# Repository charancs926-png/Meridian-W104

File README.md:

# Meridian W104

Meridian W104 is my custom full size **104-key wireless mechanical keyboard**, built around a **Seeed XIAO nRF52840 non-Plus**.

so basically i wanted a full size board with a proper number pad that could run over bluetooth, but still use usb-c when needed. the project brings together the key matrix, diodes, serial scan logic, battery connection and a slim rounded case. the hardware is in KiCad and the case source is in Fusion 360, with the files needed to make a first prototype included here.

## why i made this

i wanted to understand how a complete keyboard fits together, from what happens when a switch closes to how that key reaches the computer. keeping the numpad and navigation block was important, and i wanted the enclosure to feel like one finished design instead of a box around a PCB.

main goals for this project :

- make a full size ANSI board with 104 keys, navigation keys and numpad
- use **Bluetooth LE** with a protected single-cell battery, plus usb-c
- scan the large matrix using one 74HC595 and three 74HC165 registers
- keep the schematic on one sheet and the board routing orderly
- build a slim rounded case with a bronze seam accent and concealed screws
- learn the complete sequence: schematic → PCB layout → CAD → fabrication → firmware bring-up

the tricky parts were making the matrix and firmware agree, keeping the radio antenna clear, and checking that the screws and battery actually fit the case. those checks matter just as much as the overall appearance.

## project status

this is the final digital **V1 first-prototype fabrication package**. the latest review on 9 October 2026 passed the configured KiCad electrical and board checks with zero errors and zero unconnected items. firmware simulation covers all 104 populated keys. the five printable meshes are closed, and the retained full STEP check covers 219 valid solids. physical soldering, typing, BLE range, charging and print-fit testing are the next stage.

whats included :

- editable KiCad project, one-page schematic, PCB, local libraries and 104 linked switch models
- complete assembly `.step`
- five printable `.stl` parts, with printing and assembly instructions
- Gerber/drill ZIP, assembly BOM, placement files and release checks
- CircuitPython USB/BLE firmware and a matrix diagnostic
- schematic/PCB PDFs, project images, cart evidence

current hardware summary :

| | |
|---|---|
| Layout | full size ANSI, 104 keys including nav block and numpad |
| Controller | Seeed XIAO nRF52840, original non-Plus |
| Connectivity | Bluetooth LE and usb-c; rear mode button switches transport |
| Matrix | 6 rows × 22 columns, 104 populated positions |
| Scan logic | 1× 74HC595 row register, 3× 74HC165 column registers, 3.3V |
| Diodes | 104× 1N4148W, one per switch |
| Battery | protected 3.7V 500mAh 502248P, with a separate PH2.0 pigtail |
| Indicators | Caps Lock, Num Lock and Scroll Lock; Num LED blinks while waiting for BLE |
| Stabilizers | Durock V2 PCB screw-in set: seven 2U plus one 6.25U |
| Switches | soldered MX-compatible PCB pattern; listed Haku pack selection |
| Keycaps | ANSI MX set with 6.25U spacebar; white Cherry-profile selection |
| Case | rounded printed bottom, frame, plate, bronze accent and mode-button cap |
| PCB | four copper layers, 1.6mm FR4; nominal 458.15 × 164mm |

the Meridian look comes from the rounded frame, recessed rear controls and thin accent seam. the white keycaps keep the full size layout easy to read. these are design renders; a finished physical keyboard has not been photographed yet.

## images

### full 3d model

### indicator leds (caps / num / scroll)

the three lock indicators sit in the rear strip. the PCB view also shows the switches and controller placement.

### pcb

### schematic / wiring

the complete matrix, XIAO, four scan registers, battery wiring, switches and lock indicators are on one A2 sheet. the [PDF](PDFs/Meridian%20W104.pdf) can be zoomed to read individual values and pins.

### other screenshots

some more views of the case and plate from Fusion :

## repo file checklist

important files in this repo :

- `PCB/Meridian W104.kicad_pro`
- `PCB/Meridian W104.kicad_sch`
- `PCB/Meridian W104.kicad_pcb`
- `PCB/3D Models/` — portable switch models and attribution
- `CAD/Full Meridian W104/Meridian W104.step`
- `CAD/Printing Files/` — `Bottom.stl`, `Plate.stl`, `Top Frame.stl`, `Bronze Seam Accent.stl`, `Mode Button.stl`
- `Firmware/boot.py`, `code.py`, `scanner.py`, `keymap.py`, `matrix_diagnostic.py`
- `Fabrication/Assembly BOM.csv`
- `Fabrication/Component Positions.csv` and `SMD Positions.csv`
- `Fabrication/netlist.ipc` — IPC-D-356 bare-board test netlist
- `Fabrication/Meridian-W104-PCB-Fabrication.zip`
- `Fabrication/Gerbers/` — individual plots, job and drill files
- `bom.csv`
- `PDFs/Meridian W104.pdf` — chematic page
- `PDFs/PCB Editor.pdf` — PCB layer pages
- `JOURNAL.md`

## cad

the case source is in **Fusion 360**, with a full `.step` export in `CAD/Full Meridian W104/`. only the five parts that need printing are in `CAD/Printing Files/`. all dimensions are millimetres; the largest part spans **466.15mm**, so the printer needs enough real usable bed area, including space for a brim.

## firmware note

the firmware is **CircuitPython** with a custom serial-matrix scanner. the normal files are `boot.py`, `code.py`, `scanner.py` and `keymap.py`; `matrix_diagnostic.py` is the separate bring-up tool.

install the official [XIAO nRF52840 CircuitPython build](https://circuitpython.org/board/Seeed_XIAO_nRF52840_Sense/) after checking that page's bootloader prerequisite, then copy the four normal files and `adafruit_ble`, `adafruit_hid` plus their dependencies from the matching [library bundle](https://circuitpython.org/libraries) to `CIRCUITPY`. the family download also covers the original non-Sense module used here.

usb insertion/removal selects the available transport. a short press and release of the rear mode button toggles USB/BLE; holding it for five seconds clears BLE bonding. the advertised name is **Meridian W104**. reports support six ordinary keys plus modifiers. test the diagnostic with all 104 real switches before closing the case; simulation is already passing, but soldered hardware still needs bring-up.

## bom (summary)

full BOM is in `bom.csv`. these are recorded carts, supplier listings and a PCB quote, **not a record of paid orders**. prices below are totals for each row, including the stated retailer packs; the CSV notes explain fitted quantities and spares.

| # | Name | Purpose | Qty | Cost (INR) | Cost ($) | Distributor | Link |
|---|---|---|---:|---:|---:|---|---|
| 1 | XIAO nRF52840 non-Plus | BLE / USB controller and module charger | 1 | 1,451.00 | 15.06 | LionCircuits | [View](https://www.lioncircuits.com/parts/102010448) |
| 2 | SN74HC595D SOIC-16 | 6 row sink outputs | 1 | 32.20 | 0.33 | KTRON | [View](https://www.ktron.in/product/74hc595d-8-bit-shift-register-ic-smd/) |
| 3 | SN74HC165D SOIC-16 | 22 column samples | 3 | 59.40 | 0.62 | KTRON | [View](https://www.ktron.in/product/74hc165d-ic-8-bit-shift-register-soic-16-nxp/) |
| 4 | Cherry MX PCB-pattern switch, 5-pin | Soldered keys | 104 | 3,850.00 | 39.96 | StacksKB | [View](https://stackskb.com/store/menel-eight-nine-haku-linear-switch-pack-of-10/) |
| 5 | 1N4148W SOD-123 | Per-key isolation | 104 | 108.16 | 1.12 | Robu | [View](https://robu.in/product/1n4148w-slkor-75v-1v-4ns-150ma-sod-123-switching-diodes-rohs/) |
| 6 | 22k 0805 1% resistor | Column bias | 22 | 10.08 | 0.10 | Robu | [View](https://robu.in/product/ac0805fr-0722kl-yageo-res-thick-film-0805-22k-ohm-1-0-125w1-8w-%c2%b1100ppm-c-pad-smd-t-r-automotive-aec-q200/) |
| 7 | 1k 0805 resistor | Lock indicator current limit | 3 | 13.80 | 0.14 | Robu | [View](https://robu.in/product/rc0805jr-071kl-yageo-res-thick-film-0805-1k-ohm-5-0-125w1-8w-%c2%b1100ppm-c-pad-smd-t-r/) |
| 8 | 100k 0805 resistor | Row output enable default OFF | 1 | 13.50 | 0.14 | Robu | [View](https://robu.in/product/0805w8f1003t5e-uniohm-royal-ohm-125mw-thick-film-resistors-150v-%c2%b1100ppm-%e2%84%83%c2%b11-100k%cf%89-0805-chip-resistor-surface-mount-rohs/) |
| 9 | 100n 0805 X7R, 10V or above | Logic decoupling | 4 | 30.00 | 0.31 | Flyrobo | [View](https://www.flyrobo.in/0805-100nf-50v-chip-capacitors) |
| 10 | 10u 0805 X5R, 10V or above | Rail bulk capacitor | 1 | 10.60 | 0.11 | Robu | [View](https://robu.in/product/08053d106kat2a-kyocera-avx-smd-multilayer-ceramic-capacitor-10-%c2%b5f-25-v-0805-2012-metric-%c2%b1-10-x5r/) |
| 11 | 3mm LED, diffused, Vf compatible with 3.3V | Caps / Num / Scroll indicators | 3 | 18.80 | 0.20 | KTRON | [View](https://www.ktron.in/product/red-led-red-diffusion-3mm-th/) |
| 12 | JST PH S2B-PH-K horizontal 2-pin | Battery connector | 1 | 16.00 | 0.17 | Robu | [View](https://robu.in/product/s2b-ph-klfsn-jst-1x2p-2p-ph-tin-2-25%e2%84%8385%e2%84%83-2a-1-2mm-brass-bend-insert-push-pullp2mm-wire-to-board-connector-rohs/) |
| 13 | PCM12-pattern SMD SPDT slide switch | Battery disconnect | 1 | 66.00 | 0.68 | Robu | [View](https://robu.in/product/pcm12smtr-ck-standing-paste-single-pole-double-throw-spdt-6v-smd-slide-switches-rohs/) |
| 14 | 6mm THT tactile pushbutton | Transport toggle / bond reset | 1 | 3.00 | 0.03 | Tomson | [View](https://www.tomsonelectronics.com/products/tactile-push-button-micro-switch-6x6x4-3mm) |
| 15 | Protected 3.7V 500mAh LiPo 502248P (bare leads) | Wireless power; maximum assembled envelope 60x28x6mm | 1 | 299.00 | 3.10 | Probots | [View](https://probots.co.in/3-7v-500mah-lipo-battery-502248-open-ended.html) |
| 16 | JST-PH2.0 2-pin female pigtail to bare wire | Adapt protected bare-lead battery to J1 | 1 | 4.13 | 0.04 | Hubtronics | [View](https://hubtronics.in/connectors/relimate_connectors/board_to_wire_relimate/1508) |
| 17 | 7-pin 2.54mm headers | Module mounting; two rows | 2 | 40.00 | 0.42 | Flyrobo | [View](https://www.flyrobo.in/40-pin-male-header-connector-strip-breakable-5pcs) |
| 18 | Flexible insulated wire | Module underside BAT+ / BAT- leads | 2 | 24.00 | 0.25 | Robu | [View](https://robu.in/product/high-quality-ultra-flexible-28awg-silicone-wire-1000m-red/) |
| 19 | ANSI 104-key MX keycap set | User keycaps; 6.25u spacebar | 1 | 1,000.00 | 10.38 | StacksKB | [View](https://stackskb.com/store/stackspbt-blank-white-cherry-profile-keycaps-113-key/) |
| 20 | Durock V2 PCB screw-in stabilizer kit (7x2U + 1x6.25U) | Seven wide keys and 6.25U spacebar | 1 | 2,365.00 | 24.54 | StacksKB | [View](https://stackskb.com/store/durock-clear-screw-in-stabilizers-v2/?attribute_combination=7%2B1+Set&attribute_spacebar-size=6.25U) |
| 21 | M3x30mm DIN912 socket-head SS304 screws (10pc pack) | 3 concealed rear mounts | 1 | 116.00 | 1.20 | RPI Shop | [View](https://rpishop.in/products/ss-allen-cap-m3?variant=45146051510424) |
| 22 | M3x15mm DIN912 socket-head SS304 screws (10pc pack) | 3 concealed front mounts | 1 | 88.00 | 0.91 | RPI Shop | [View](https://rpishop.in/products/ss-allen-cap-m3?variant=45146051412120) |
| 23 | M3x20mm DIN912 socket-head SS304 screws (10pc pack) | 1 concealed centre mounts | 1 | 92.00 | 0.95 | RPI Shop | [View](https://rpishop.in/products/ss-allen-cap-m3?variant=45146051444888) |
| 24 | M3 insert assortment; select 5mm long x4.2mm OD | Seven top-frame bosses, 3.9mm pilot holes | 1 | 1,519.00 | 15.76 | Robu | [View](https://robu.in/product/brass-heat-set-insert-nut-hot-melt-knurled-threaded-m3-400pcs-kit/) |
| 25 | Meridian W104 four-layer PCB, 1.6mm | Final checked four-layer Gerber and drill package | 5 | 8,647.58 | 89.25 | JLCPCB | [View](https://cart.jlcpcb.com/shopcart/cart/) |
| 26 | Printed case set | Bottom, plate, top frame, seam accent, mode button | 1 | 0.00 | 0.00 | Printing Legion | [View](https://printlegion.hackclub.com/) |

**listed BOM total : ₹19,877.25 / $205.77**

---

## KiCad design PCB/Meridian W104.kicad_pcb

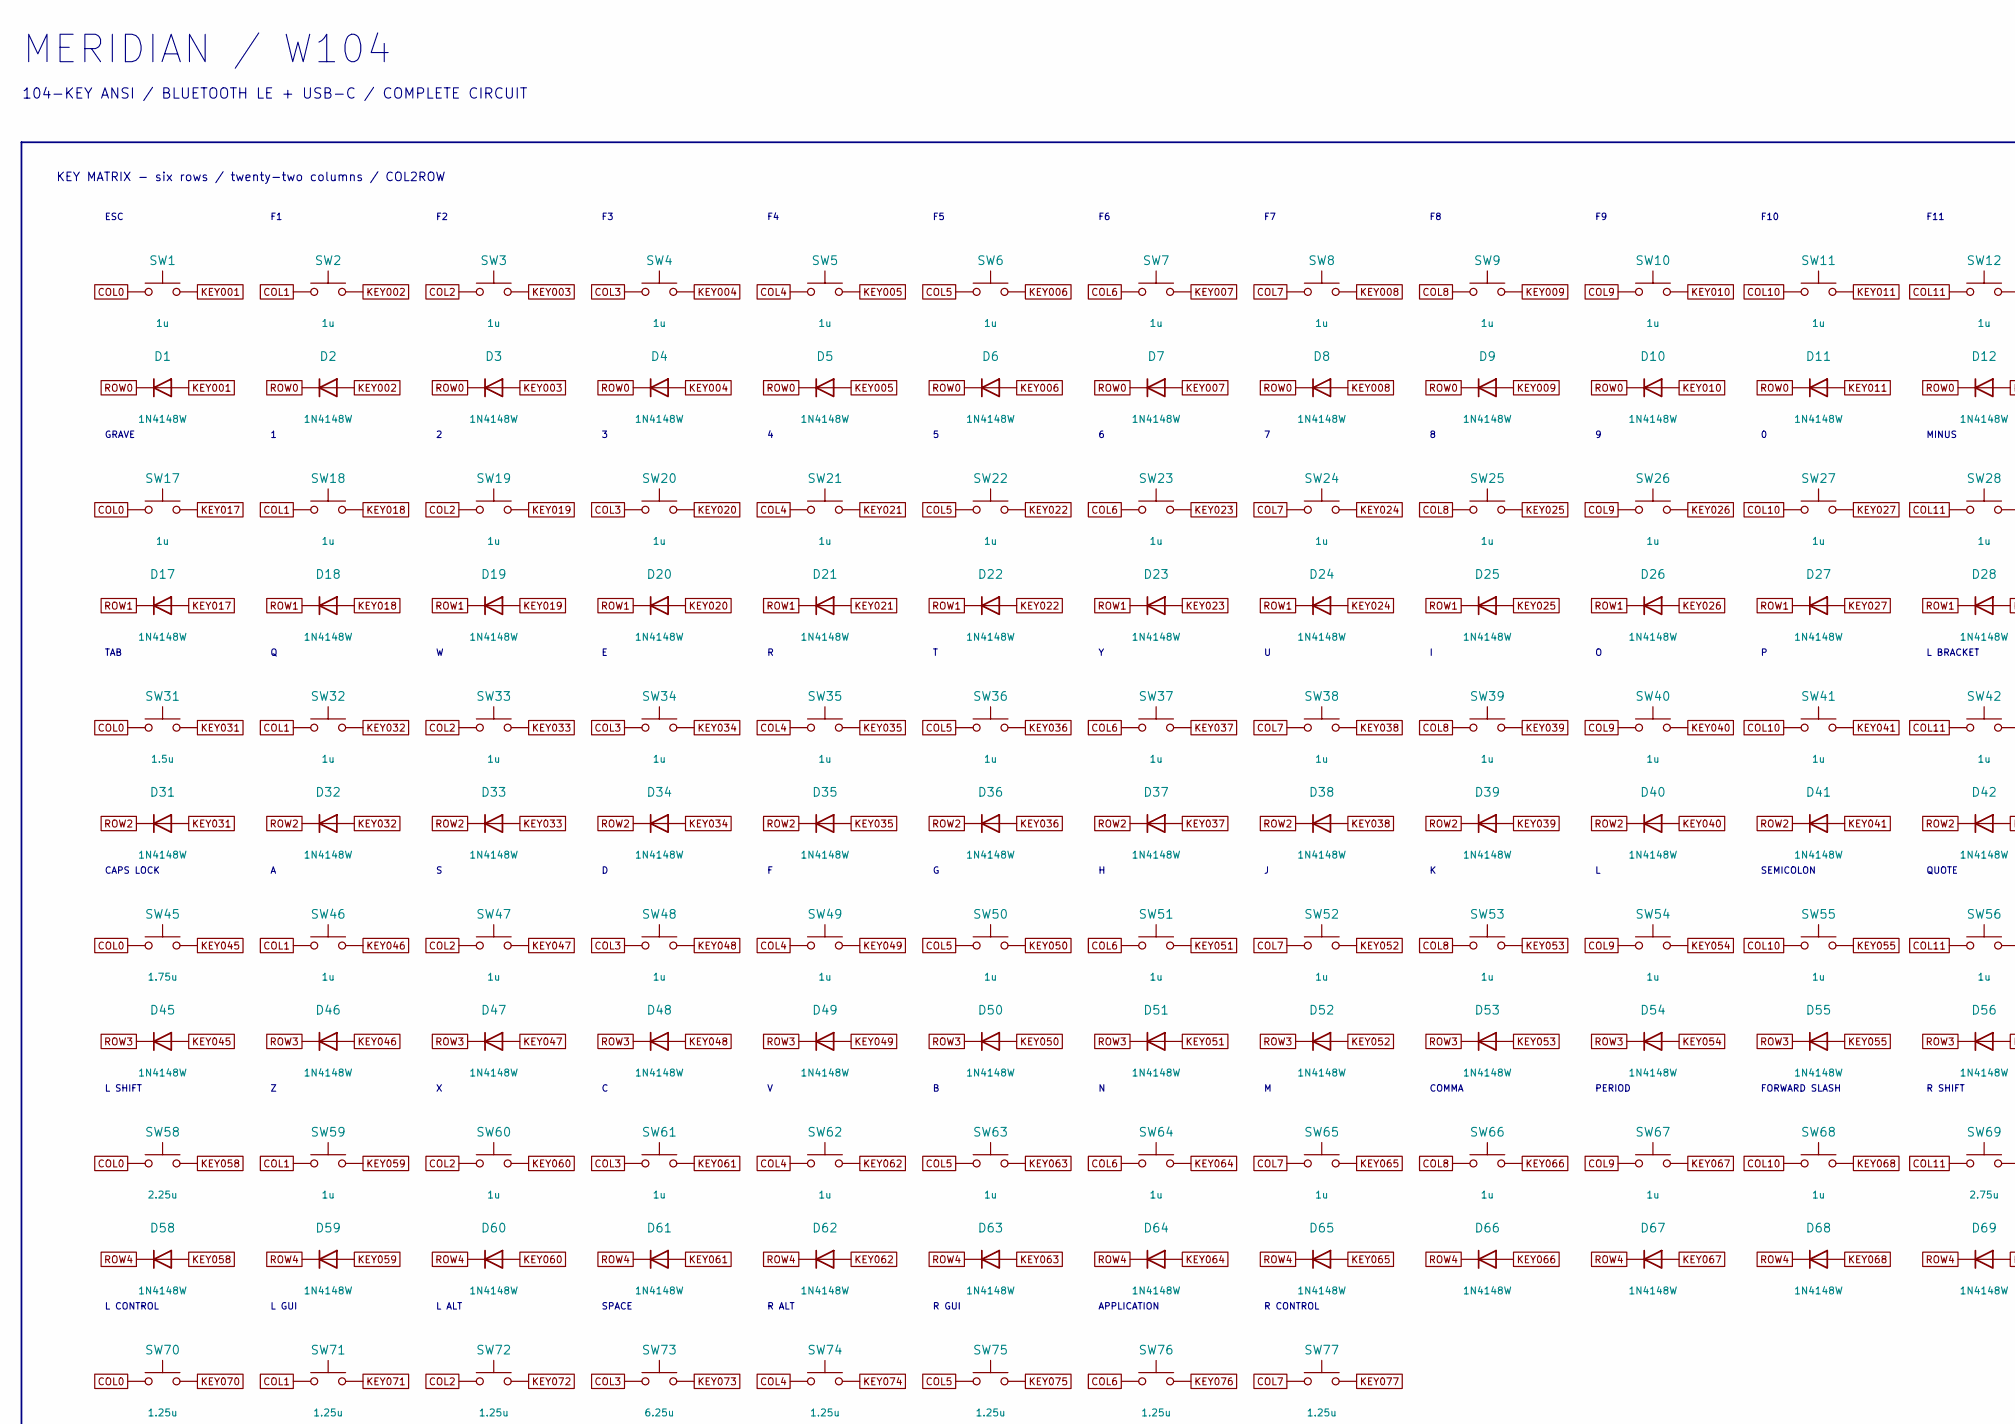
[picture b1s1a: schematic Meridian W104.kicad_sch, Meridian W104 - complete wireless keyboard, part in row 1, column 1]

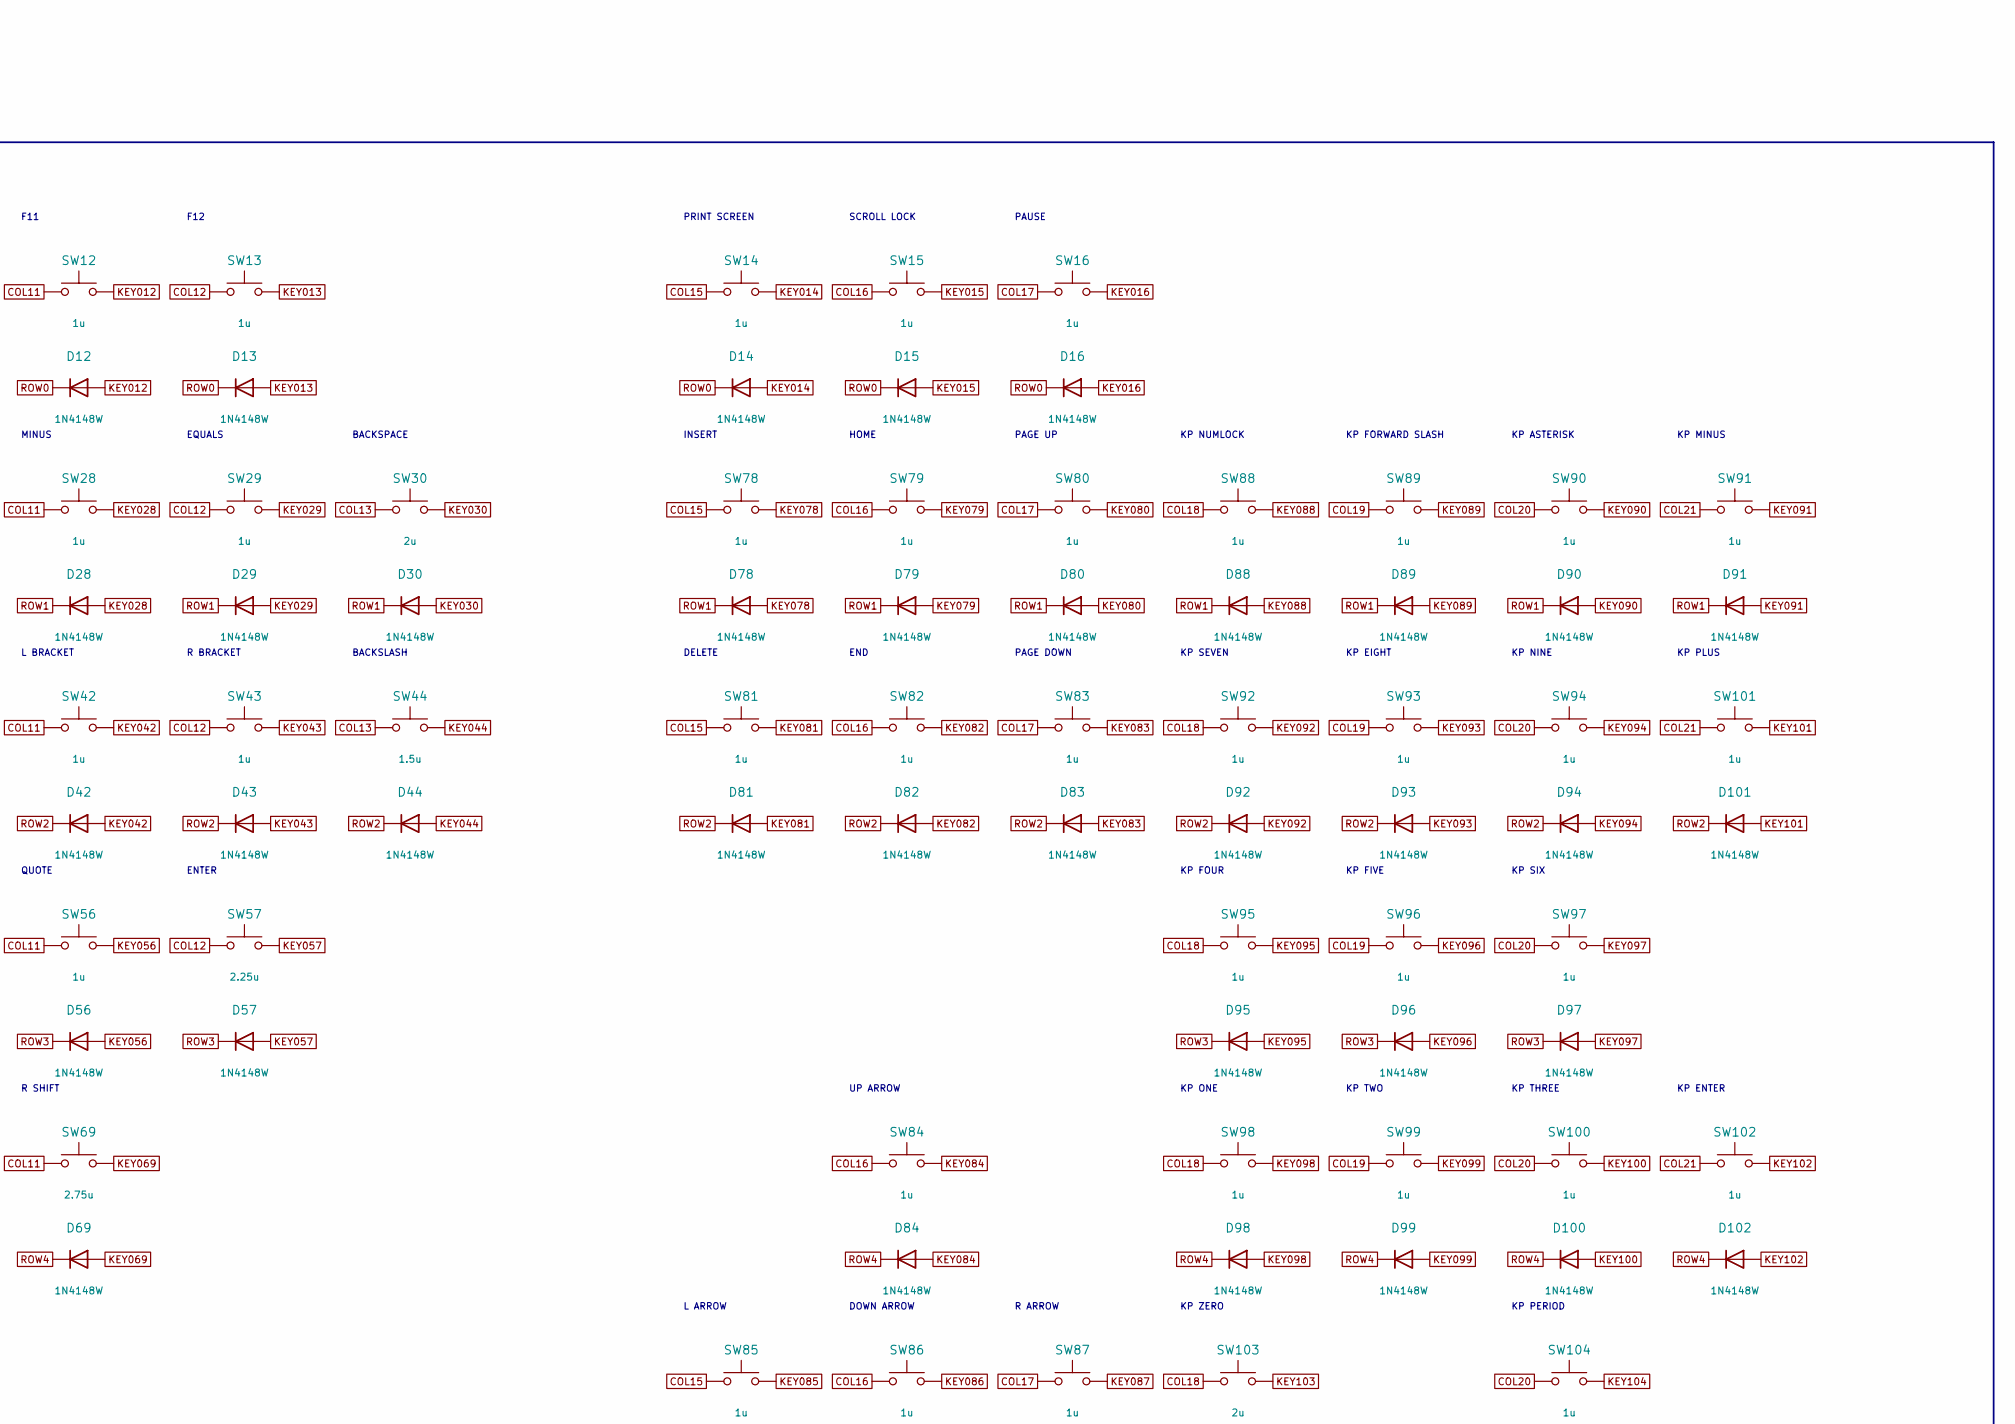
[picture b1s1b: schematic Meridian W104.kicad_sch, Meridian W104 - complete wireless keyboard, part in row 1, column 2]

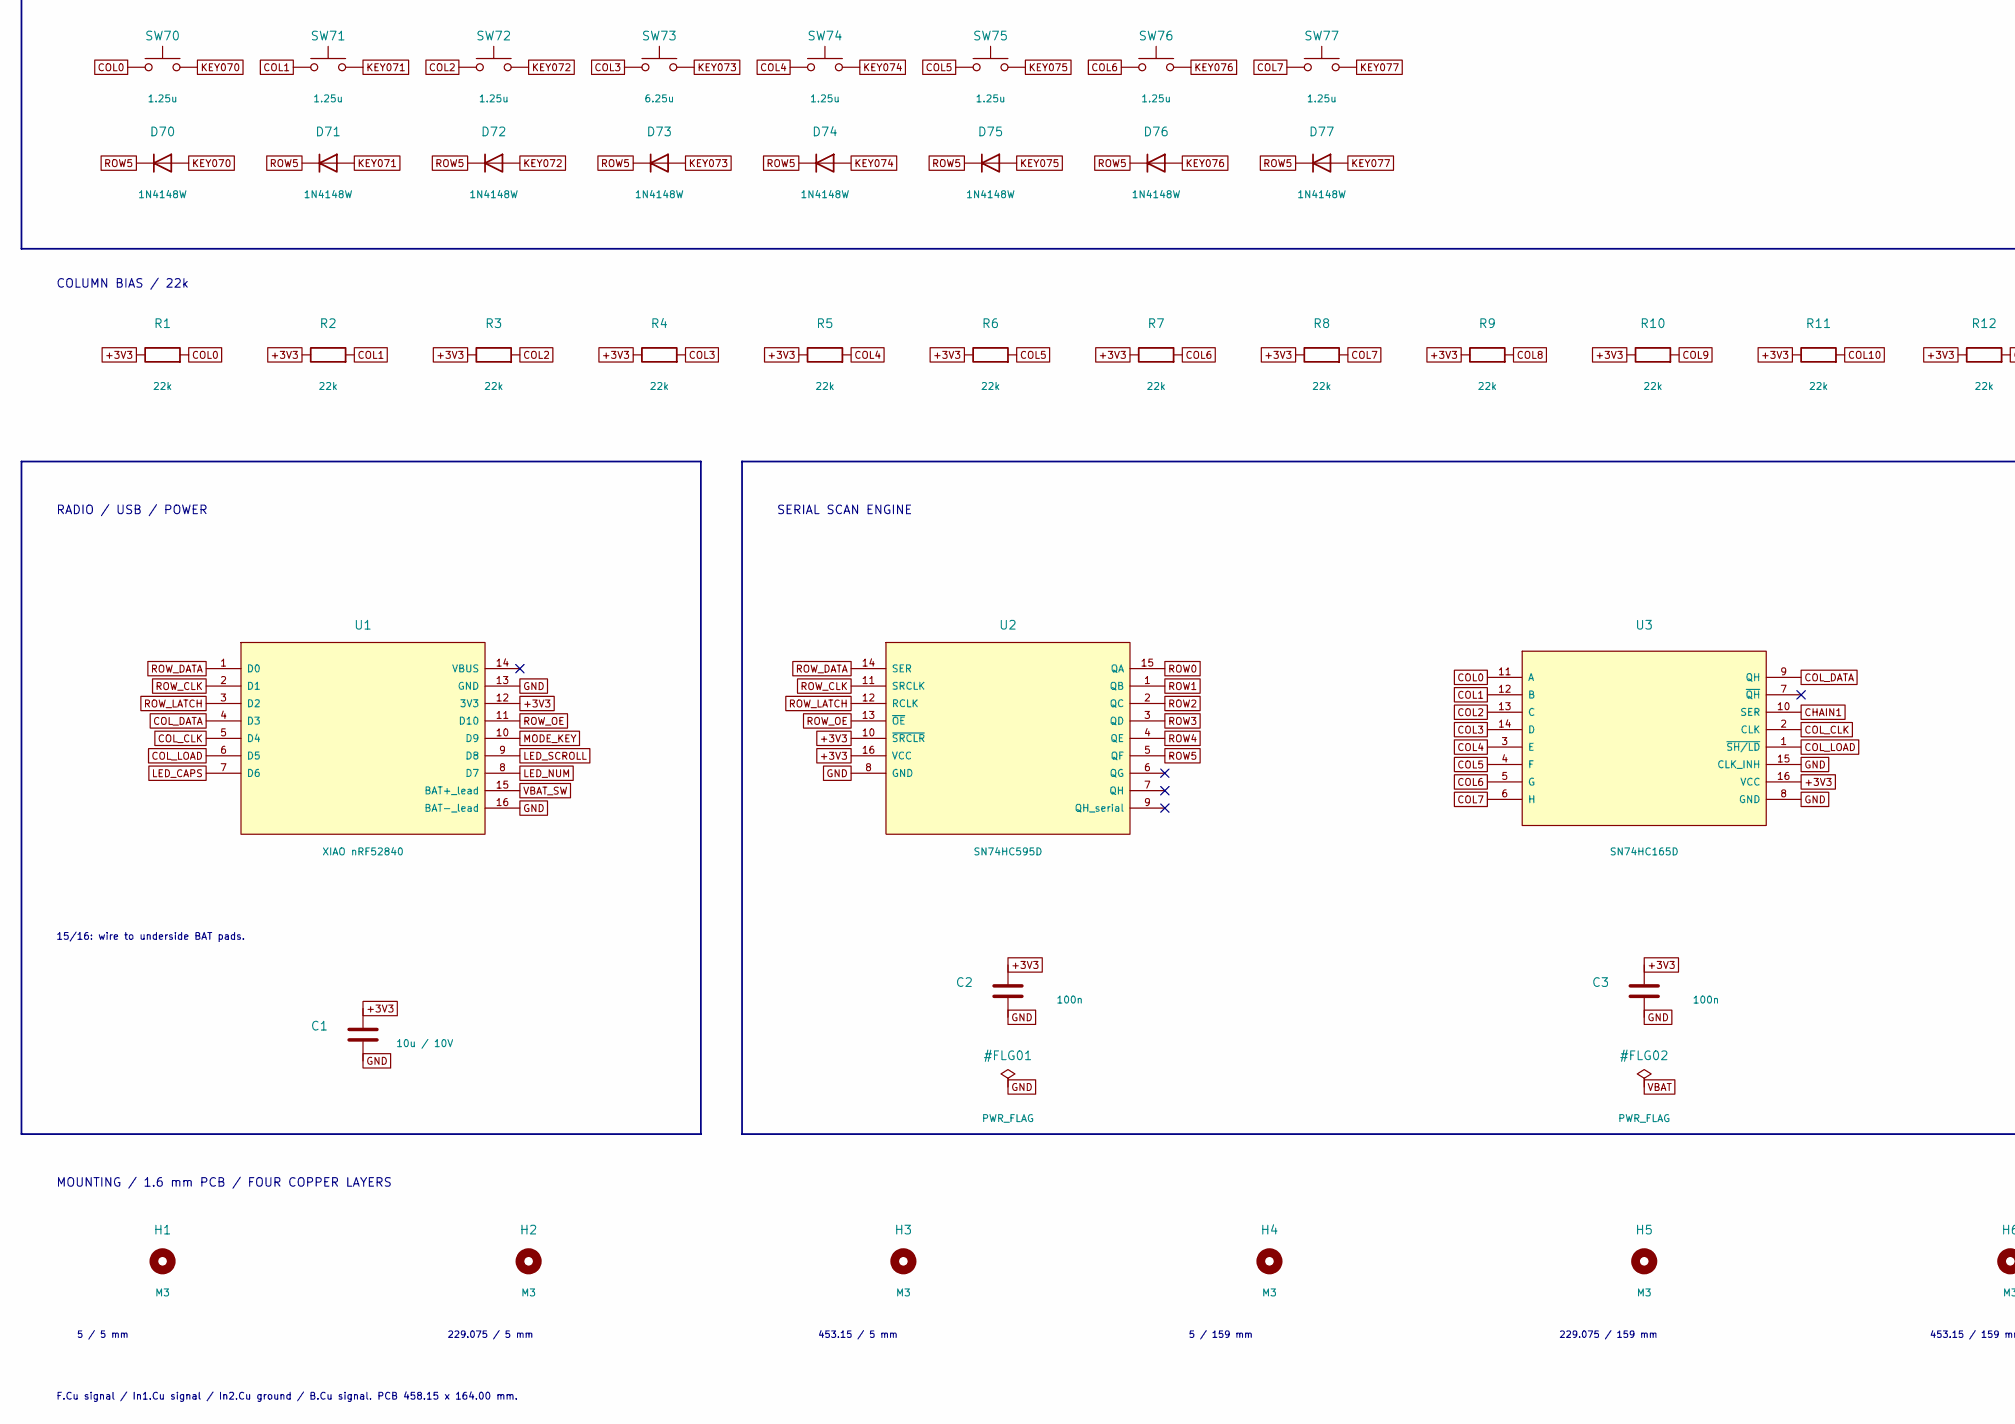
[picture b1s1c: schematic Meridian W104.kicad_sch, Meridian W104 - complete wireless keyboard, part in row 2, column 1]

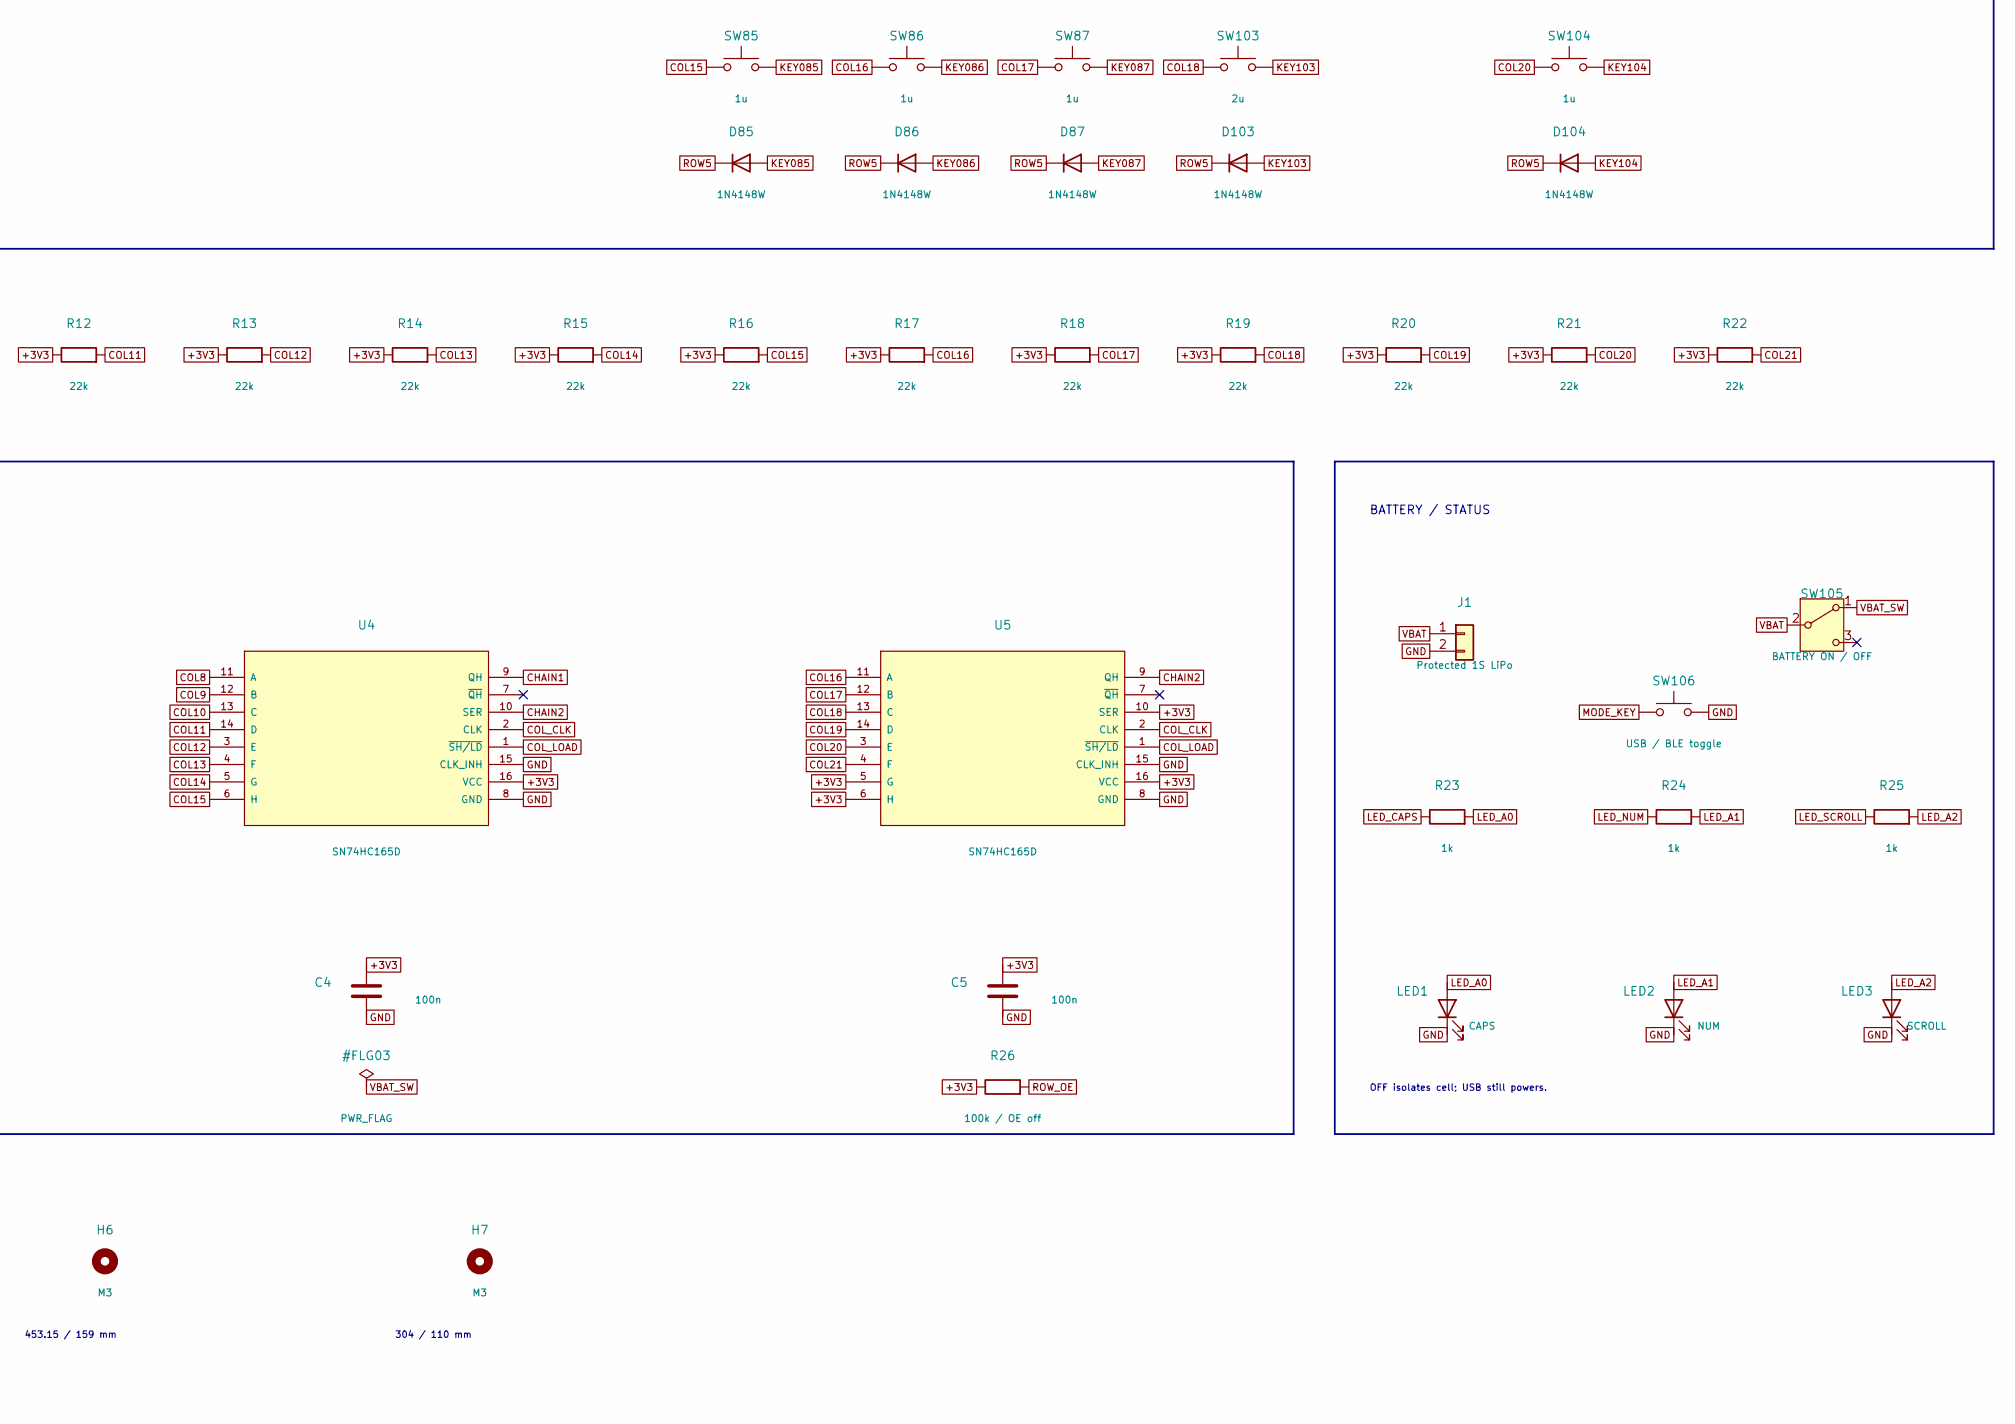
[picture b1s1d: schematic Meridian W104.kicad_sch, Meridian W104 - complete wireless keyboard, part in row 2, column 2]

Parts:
C1: 10u / 10V; C_0805_2012Metric
C2, C3, C4, C5: 100n; C_0805_2012Metric
D1, D2, D3, D4, D5, D6, D7, D8, D9, D10, D11, D12, D13, D14, D15, D16, D17, D18, D19, D20, D21, D22, D23, D24, D25, D26, D27, D28, D29, D30, D31, D32, D33, D34, D35, D36, D37, D38, D39, D40, D41, D42, D43, D44, D45, D46, D47, D48, D49, D50, D51, D52, D53, D54, D55, D56, D57, D58, D59, D60, D61, D62, D63, D64, D65, D66, D67, D68, D69, D70, D71, D72, D73, D74, D75, D76, D77, D78, D79, D80, D81, D82, D83, D84, D85, D86, D87, D88, D89, D90, D91, D92, D93, D94, D95, D96, D97, D98, D99, D100, D101, D102, D103, D104: 1N4148W; D_SOD-123
H1, H2, H3, H4, H5, H6, H7: M3; MountingHole_3.2mm_M3
J1: Protected 1S LiPo; JST_PH_S2B-PH-K_1x02_P2.00mm_Horizontal
LED1: CAPS; LED_D3.0mm
LED2: NUM; LED_D3.0mm
LED3: SCROLL; LED_D3.0mm
R1, R2, R3, R4, R5, R6, R7, R8, R9, R10, R11, R12, R13, R14, R15, R16, R17, R18, R19, R20, R21, R22: 22k; R_0805_2012Metric
R23, R24, R25: 1k; R_0805_2012Metric
R26: 100k / OE off; R_0805_2012Metric
SW1, SW2, SW3, SW4, SW5, SW6, SW7, SW8, SW9, SW10, SW11, SW12, SW13, SW14, SW15, SW16, SW17, SW18, SW19, SW20, SW21, SW22, SW23, SW24, SW25, SW26, SW27, SW28, SW29, SW32, SW33, SW34, SW35, SW36, SW37, SW38, SW39, SW40, SW41, SW42, SW43, SW46, SW47, SW48, SW49, SW50, SW51, SW52, SW53, SW54, SW55, SW56, SW59, SW60, SW61, SW62, SW63, SW64, SW65, SW66, SW67, SW68, SW78, SW79, SW80, SW81, SW82, SW83, SW84, SW85, SW86, SW87, SW88, SW89, SW90, SW91, SW92, SW93, SW94, SW95, SW96, SW97, SW98, SW99, SW100, SW104: 1u; SW_Cherry_MX_1.00u_PCB
SW30, SW103: 2u; SW_Cherry_MX_2.00u_PCB
SW31, SW44: 1.5u; SW_Cherry_MX_1.50u_PCB
SW45: 1.75u; SW_Cherry_MX_1.75u_PCB
SW57, SW58: 2.25u; SW_Cherry_MX_2.25u_PCB
SW69: 2.75u; SW_Cherry_MX_2.75u_PCB
SW70, SW71, SW72, SW74, SW75, SW76, SW77: 1.25u; SW_Cherry_MX_1.25u_PCB
SW73: 6.25u; SW_Cherry_MX_6.25u_PCB
SW101, SW102: 1u; SW_Cherry_MX_2.00u_Vertical_PCB
SW105: BATTERY ON / OFF; SW_SPDT_PCM12
SW106: USB / BLE toggle; SW_PUSH_6mm
U1: XIAO nRF52840; XIAO_Carrier
U2: SN74HC595D; SOIC-16_3.9x9.9mm_P1.27mm
U3, U4, U5: SN74HC165D; SOIC-16_3.9x9.9mm_P1.27mm

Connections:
+3V3: C1.1, C2.1, C3.1, C4.1, C5.1, R1.1, R2.1, R3.1, R4.1, R5.1, R6.1, R7.1, R8.1, R9.1, R10.1, R11.1, R12.1, R13.1, R14.1, R15.1, R16.1, R17.1, R18.1, R19.1, R20.1, R21.1, R22.1, R26.1, U1.12 (3V3), U2.10 (~SRCLR), U2.16 (VCC), U3.16 (VCC), U4.16 (VCC), U5.5 (G), U5.6 (H), U5.10 (SER), U5.16 (VCC)
CHAIN1: U3.10 (SER), U4.9 (QH)
CHAIN2: U4.10 (SER), U5.9 (QH)
COL0: R1.2, SW1.1, SW17.1, SW31.1, SW45.1, SW58.1, SW70.1, U3.11 (A)
COL1: R2.2, SW2.1, SW18.1, SW32.1, SW46.1, SW59.1, SW71.1, U3.12 (B)
COL2: R3.2, SW3.1, SW19.1, SW33.1, SW47.1, SW60.1, SW72.1, U3.13 (C)
COL3: R4.2, SW4.1, SW20.1, SW34.1, SW48.1, SW61.1, SW73.1, U3.14 (D)
COL4: R5.2, SW5.1, SW21.1, SW35.1, SW49.1, SW62.1, SW74.1, U3.3 (E)
COL5: R6.2, SW6.1, SW22.1, SW36.1, SW50.1, SW63.1, SW75.1, U3.4 (F)
COL6: R7.2, SW7.1, SW23.1, SW37.1, SW51.1, SW64.1, SW76.1, U3.5 (G)
COL7: R8.2, SW8.1, SW24.1, SW38.1, SW52.1, SW65.1, SW77.1, U3.6 (H)
COL8: R9.2, SW9.1, SW25.1, SW39.1, SW53.1, SW66.1, U4.11 (A)
COL9: R10.2, SW10.1, SW26.1, SW40.1, SW54.1, SW67.1, U4.12 (B)
COL10: R11.2, SW11.1, SW27.1, SW41.1, SW55.1, SW68.1, U4.13 (C)
COL11: R12.2, SW12.1, SW28.1, SW42.1, SW56.1, SW69.1, U4.14 (D)
COL12: R13.2, SW13.1, SW29.1, SW43.1, SW57.1, U4.3 (E)
COL13: R14.2, SW30.1, SW44.1, U4.4 (F)
COL14: R15.2, U4.5 (G)
COL15: R16.2, SW14.1, SW78.1, SW81.1, SW85.1, U4.6 (H)
COL16: R17.2, SW15.1, SW79.1, SW82.1, SW84.1, SW86.1, U5.11 (A)
COL17: R18.2, SW16.1, SW80.1, SW83.1, SW87.1, U5.12 (B)
COL18: R19.2, SW88.1, SW92.1, SW95.1, SW98.1, SW103.1, U5.13 (C)
COL19: R20.2, SW89.1, SW93.1, SW96.1, SW99.1, U5.14 (D)
COL20: R21.2, SW90.1, SW94.1, SW97.1, SW100.1, SW104.1, U5.3 (E)
COL21: R22.2, SW91.1, SW101.1, SW102.1, U5.4 (F)
COL_CLK: U1.5 (D4), U3.2 (CLK), U4.2 (CLK), U5.2 (CLK)
COL_DATA: U1.4 (D3), U3.9 (QH)
COL_LOAD: U1.6 (D5), U3.1 (~SH/LD), U4.1 (~SH/LD), U5.1 (~SH/LD)
GND: C1.2, C2.2, C3.2, C4.2, C5.2, J1.2, LED1.1 (K), LED2.1 (K), LED3.1 (K), SW106.2, U1.13 (GND), U1.16 (BAT-_lead), U2.8 (GND), U3.8 (GND), U3.15 (CLK_INH), U4.8 (GND), U4.15 (CLK_INH), U5.8 (GND), U5.15 (CLK_INH)
KEY001: D1.2 (A), SW1.2
KEY002: D2.2 (A), SW2.2
KEY003: D3.2 (A), SW3.2
KEY004: D4.2 (A), SW4.2
KEY005: D5.2 (A), SW5.2
KEY006: D6.2 (A), SW6.2
KEY007: D7.2 (A), SW7.2
KEY008: D8.2 (A), SW8.2
KEY009: D9.2 (A), SW9.2
KEY010: D10.2 (A), SW10.2
KEY011: D11.2 (A), SW11.2
KEY012: D12.2 (A), SW12.2
KEY013: D13.2 (A), SW13.2
KEY014: D14.2 (A), SW14.2
KEY015: D15.2 (A), SW15.2
KEY016: D16.2 (A), SW16.2
KEY017: D17.2 (A), SW17.2
KEY018: D18.2 (A), SW18.2
KEY019: D19.2 (A), SW19.2
KEY020: D20.2 (A), SW20.2
KEY021: D21.2 (A), SW21.2
KEY022: D22.2 (A), SW22.2
KEY023: D23.2 (A), SW23.2
KEY024: D24.2 (A), SW24.2
KEY025: D25.2 (A), SW25.2
KEY026: D26.2 (A), SW26.2
KEY027: D27.2 (A), SW27.2
KEY028: D28.2 (A), SW28.2
KEY029: D29.2 (A), SW29.2
KEY030: D30.2 (A), SW30.2
KEY031: D31.2 (A), SW31.2
KEY032: D32.2 (A), SW32.2
KEY033: D33.2 (A), SW33.2
KEY034: D34.2 (A), SW34.2
KEY035: D35.2 (A), SW35.2
KEY036: D36.2 (A), SW36.2
KEY037: D37.2 (A), SW37.2
KEY038: D38.2 (A), SW38.2
KEY039: D39.2 (A), SW39.2
KEY040: D40.2 (A), SW40.2
KEY041: D41.2 (A), SW41.2
KEY042: D42.2 (A), SW42.2
KEY043: D43.2 (A), SW43.2
KEY044: D44.2 (A), SW44.2
KEY045: D45.2 (A), SW45.2
KEY046: D46.2 (A), SW46.2
KEY047: D47.2 (A), SW47.2
KEY048: D48.2 (A), SW48.2
KEY049: D49.2 (A), SW49.2
KEY050: D50.2 (A), SW50.2
KEY051: D51.2 (A), SW51.2
KEY052: D52.2 (A), SW52.2
KEY053: D53.2 (A), SW53.2
KEY054: D54.2 (A), SW54.2
KEY055: D55.2 (A), SW55.2
KEY056: D56.2 (A), SW56.2
KEY057: D57.2 (A), SW57.2
KEY058: D58.2 (A), SW58.2
KEY059: D59.2 (A), SW59.2
KEY060: D60.2 (A), SW60.2
KEY061: D61.2 (A), SW61.2
KEY062: D62.2 (A), SW62.2
KEY063: D63.2 (A), SW63.2
KEY064: D64.2 (A), SW64.2
KEY065: D65.2 (A), SW65.2
KEY066: D66.2 (A), SW66.2
KEY067: D67.2 (A), SW67.2
KEY068: D68.2 (A), SW68.2
KEY069: D69.2 (A), SW69.2
KEY070: D70.2 (A), SW70.2
KEY071: D71.2 (A), SW71.2
KEY072: D72.2 (A), SW72.2
KEY073: D73.2 (A), SW73.2
KEY074: D74.2 (A), SW74.2
KEY075: D75.2 (A), SW75.2
KEY076: D76.2 (A), SW76.2
KEY077: D77.2 (A), SW77.2
KEY078: D78.2 (A), SW78.2
KEY079: D79.2 (A), SW79.2
KEY080: D80.2 (A), SW80.2
KEY081: D81.2 (A), SW81.2
KEY082: D82.2 (A), SW82.2
KEY083: D83.2 (A), SW83.2
KEY084: D84.2 (A), SW84.2
KEY085: D85.2 (A), SW85.2
KEY086: D86.2 (A), SW86.2
KEY087: D87.2 (A), SW87.2
KEY088: D88.2 (A), SW88.2
KEY089: D89.2 (A), SW89.2
KEY090: D90.2 (A), SW90.2
KEY091: D91.2 (A), SW91.2
KEY092: D92.2 (A), SW92.2
KEY093: D93.2 (A), SW93.2
KEY094: D94.2 (A), SW94.2
KEY095: D95.2 (A), SW95.2
KEY096: D96.2 (A), SW96.2
KEY097: D97.2 (A), SW97.2
KEY098: D98.2 (A), SW98.2
KEY099: D99.2 (A), SW99.2
KEY100: D100.2 (A), SW100.2
KEY101: D101.2 (A), SW101.2
KEY102: D102.2 (A), SW102.2
KEY103: D103.2 (A), SW103.2
KEY104: D104.2 (A), SW104.2
LED_A0: LED1.2 (A), R23.2
LED_A1: LED2.2 (A), R24.2
LED_A2: LED3.2 (A), R25.2
LED_CAPS: R23.1, U1.7 (D6)
LED_NUM: R24.1, U1.8 (D7)
LED_SCROLL: R25.1, U1.9 (D8)
MODE_KEY: SW106.1, U1.10 (D9)
ROW0: D1.1 (K), D2.1 (K), D3.1 (K), D4.1 (K), D5.1 (K), D6.1 (K), D7.1 (K), D8.1 (K), D9.1 (K), D10.1 (K), D11.1 (K), D12.1 (K), D13.1 (K), D14.1 (K), D15.1 (K), D16.1 (K), U2.15 (QA)
ROW1: D17.1 (K), D18.1 (K), D19.1 (K), D20.1 (K), D21.1 (K), D22.1 (K), D23.1 (K), D24.1 (K), D25.1 (K), D26.1 (K), D27.1 (K), D28.1 (K), D29.1 (K), D30.1 (K), D78.1 (K), D79.1 (K), D80.1 (K), D88.1 (K), D89.1 (K), D90.1 (K), D91.1 (K), U2.1 (QB)
ROW2: D31.1 (K), D32.1 (K), D33.1 (K), D34.1 (K), D35.1 (K), D36.1 (K), D37.1 (K), D38.1 (K), D39.1 (K), D40.1 (K), D41.1 (K), D42.1 (K), D43.1 (K), D44.1 (K), D81.1 (K), D82.1 (K), D83.1 (K), D92.1 (K), D93.1 (K), D94.1 (K), D101.1 (K), U2.2 (QC)
ROW3: D45.1 (K), D46.1 (K), D47.1 (K), D48.1 (K), D49.1 (K), D50.1 (K), D51.1 (K), D52.1 (K), D53.1 (K), D54.1 (K), D55.1 (K), D56.1 (K), D57.1 (K), D95.1 (K), D96.1 (K), D97.1 (K), U2.3 (QD)
ROW4: D58.1 (K), D59.1 (K), D60.1 (K), D61.1 (K), D62.1 (K), D63.1 (K), D64.1 (K), D65.1 (K), D66.1 (K), D67.1 (K), D68.1 (K), D69.1 (K), D84.1 (K), D98.1 (K), D99.1 (K), D100.1 (K), D102.1 (K), U2.4 (QE)
ROW5: D70.1 (K), D71.1 (K), D72.1 (K), D73.1 (K), D74.1 (K), D75.1 (K), D76.1 (K), D77.1 (K), D85.1 (K), D86.1 (K), D87.1 (K), D103.1 (K), D104.1 (K), U2.5 (QF)
ROW_CLK: U1.2 (D1), U2.11 (SRCLK)
ROW_DATA: U1.1 (D0), U2.14 (SER)
ROW_LATCH: U1.3 (D2), U2.12 (RCLK)
ROW_OE: R26.2, U1.11 (D10), U2.13 (~OE)
VBAT: J1.1, SW105.2 (B)
VBAT_SW: SW105.1 (A), U1.15 (BAT+_lead)

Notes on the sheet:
UP ARROW
KP SEVEN
L ALT
PAUSE
EQUALS
MINUS
KEY MATRIX - six rows / twenty-two columns / COL2ROW
END
5 / 5 mm
MERIDIAN / W104
KP TWO
104-KEY ANSI / BLUETOOTH LE + USB-C / COMPLETE CIRCUIT
SPACE
DELETE
OFF isolates cell; USB still powers.
INSERT
R SHIFT
FORWARD SLASH
KP PERIOD
SEMICOLON
L GUI
KP FORWARD SLASH
L ARROW
453.15 / 5 mm
KP THREE
KP ENTER
229.075 / 159 mm
F10
R GUI
R BRACKET
SERIAL SCAN ENGINE
COMMA
KP MINUS
304 / 110 mm
BACKSLASH
KP NUMLOCK
L SHIFT
PAGE DOWN
F.Cu signal / In1.Cu signal / In2.Cu ground / B.Cu signal. PCB 458.15 x 164.00 mm.
KP PLUS
